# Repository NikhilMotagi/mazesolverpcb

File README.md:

#                                                                     MILLI MOUSE

This repo is for pcbs that were designed for mazesolver MILLIMOUSE (RIP)

The project went through many changes, some were minor some were major. Following are short discriptions about each design.

## MAZESOLVERWITHIR

u(mew)controller of choice was STM32F103C8T6 , because why not, it is faster than Arduino and has a bigger storage.

Here IR sensors acted as proximity sensors. They woud send signals when walls are in a given range.

RGB led was used to give indications and also to flash like police strobe light becuase why not *FLEXXXXXX*(later it was understood "why not").

MPU6050 was used to get orientations of the bot, so that perfect 90 degree turns could be performed.

Battery - 7.4V 2S lipo orange battery, a buck converter was used to step it down to 5V. 

Points to be noted--> 

1)IR won't always work as intended and calibaration is a nightmare as the readings change with ambient light.
2) Do not flip the PCB print while exporting PDF for both back copper. Only valid for text 

## MAZESOLVERSTM32_ULTRASONIC

KNOCK KNOCK 

Who's there ?

Ambient light 

IR's were not the greatest choice for checking distance, also there was concern about centering the bot.

SO here comes the new component HC-SR04!

The pcb had to be redesigned for ultrasonic and this time for good, the placement were done using dxf files from cad so everything was perfect.

Other unsophisticated yet time saving efforts were also explored(We all agreed pcb is the way to go).

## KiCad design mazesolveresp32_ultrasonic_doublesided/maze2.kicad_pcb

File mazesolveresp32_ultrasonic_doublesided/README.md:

This version of pcb has no component changes. A new thing that we tried was to design and fabricate a double sided pcb .
Points to be remebered are 
1) Keep the track width more than 1mm because these are not easy to DIY.
2) Remember to provide appropriate diameter vias when needed, professionally manufactured pcbs have revets that join both bottom and top layers.

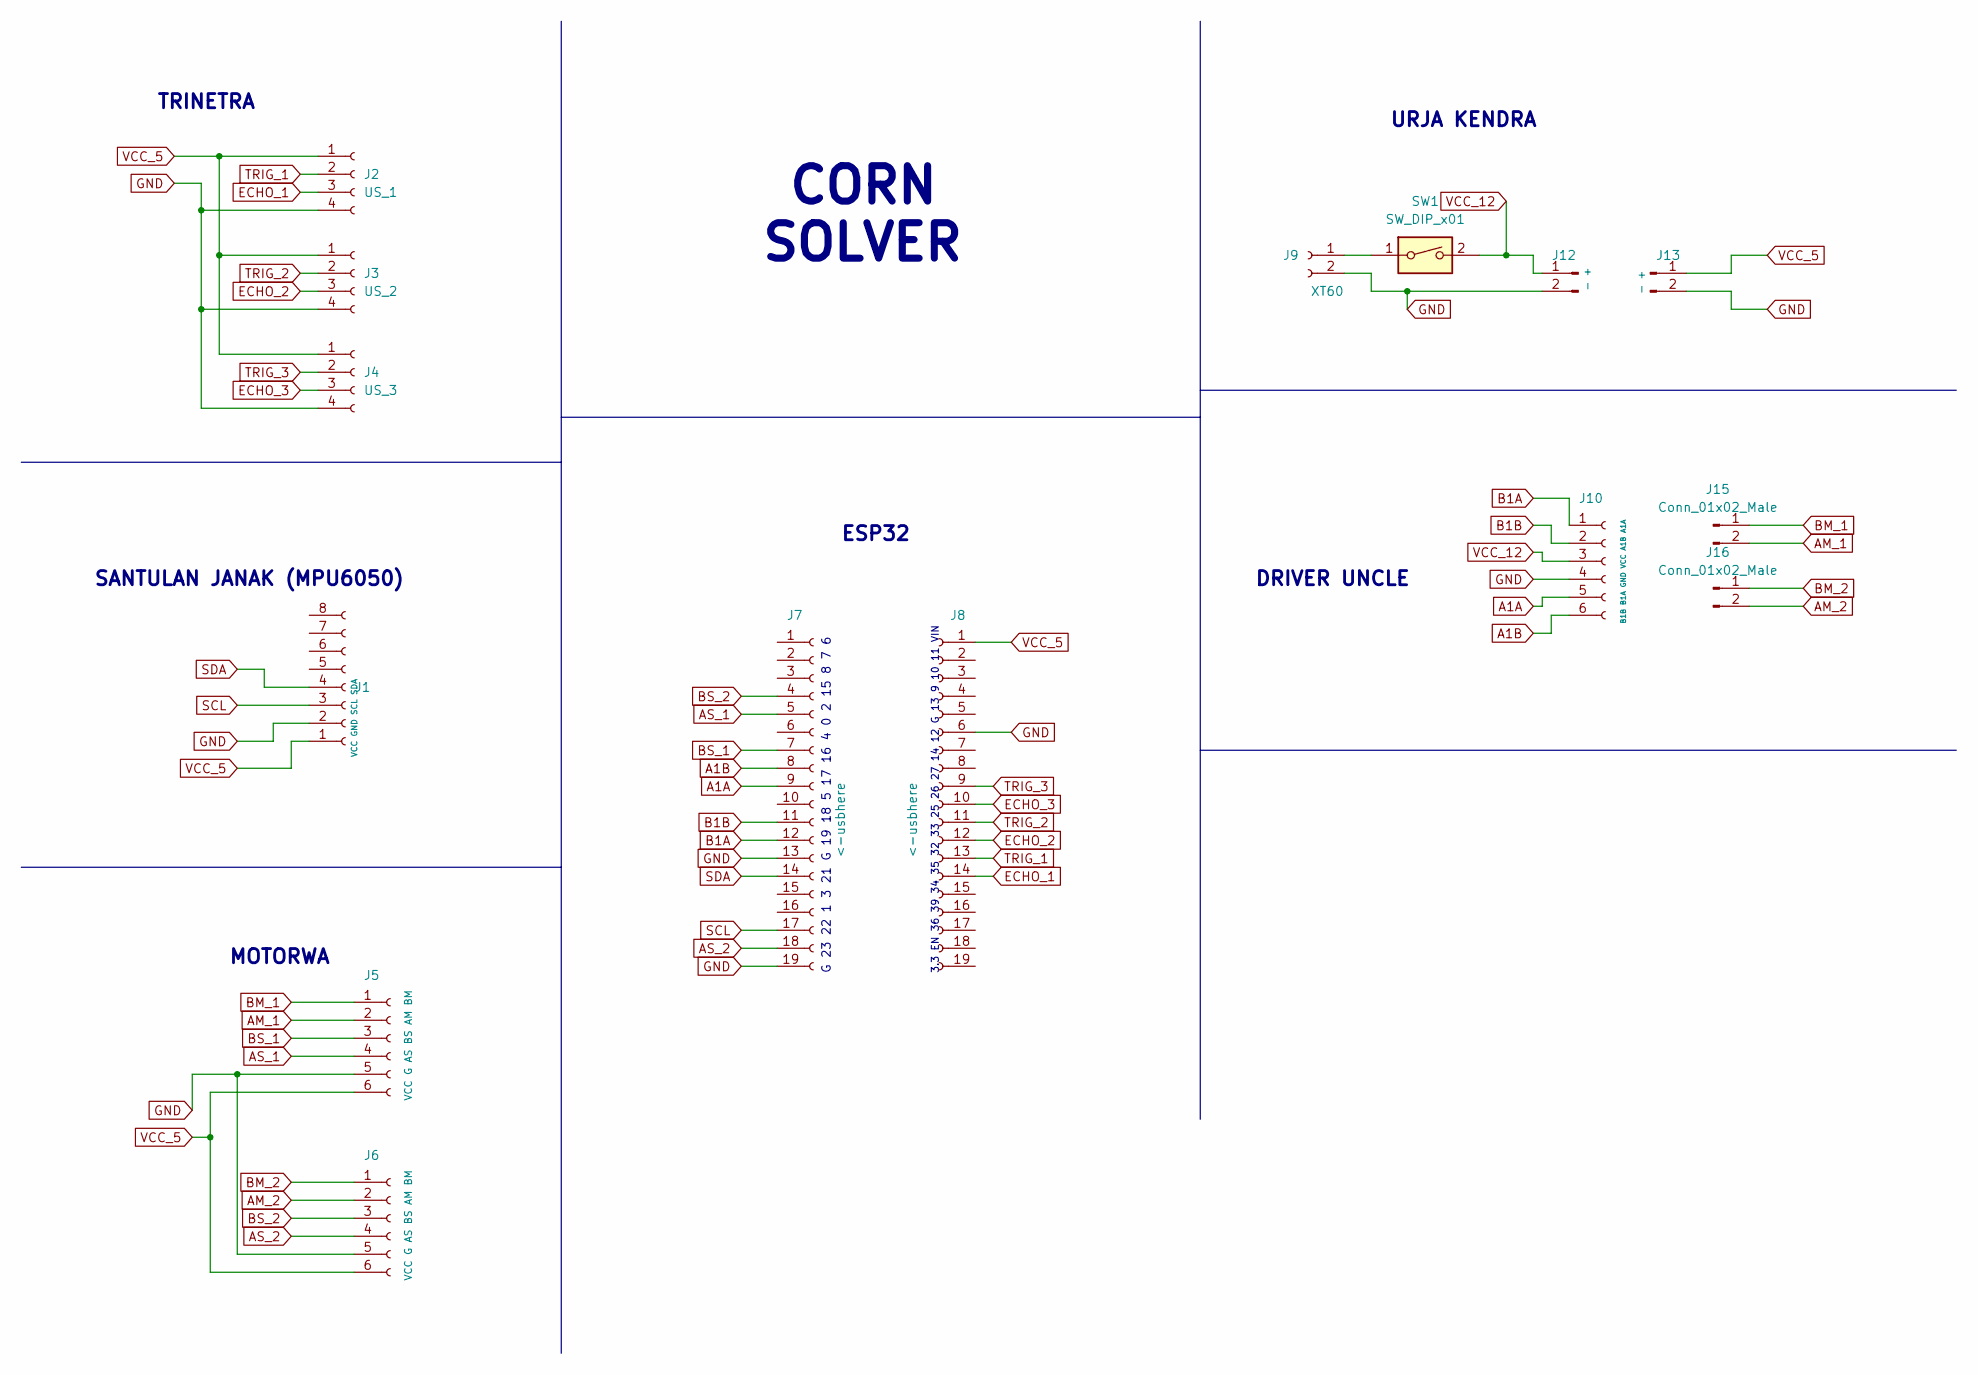
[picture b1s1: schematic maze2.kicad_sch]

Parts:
J1: VCC GND SCL SDA; PinSocket_1x08_P2.54mm_Vertical
J2: US_1; PinSocket_1x04_P2.54mm_Vertical
J3: US_2; PinSocket_1x04_P2.54mm_Vertical
J4: US_3; PinSocket_1x04_P2.54mm_Vertical
J5, J6: VCC G AS BS AM BM; PinHeader_1x06_P2.54mm_Vertical
J7, J8: <-usbhere; PinSocket_1x19_P2.54mm_Vertical
J9: XT60; AMASS_XT60-M_1x02_P7.20mm_Vertical
J10: B1B B1A GND VCC A1B A1A; PinSocket_1x06_P2.54mm_Vertical
J12, J13: - +; PinHeader_1x02_P2.54mm_Vertical
J15, J16: Conn_01x02_Male; PinSocket_1x02_P2.54mm_Vertical
SW1: SW_DIP_x01; DPDT_SW

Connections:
A1A: J7.9, J10.5
A1B: J7.8, J10.6
AM_1: J5.2, J15.2
AM_2: J6.2, J16.2
AS_1: J5.4, J7.5
AS_2: J6.4, J7.18
B1A: J7.12, J10.1
B1B: J7.11, J10.2
BM_1: J5.1, J15.1
BM_2: J6.1, J16.1
BS_1: J5.3, J7.7
BS_2: J6.3, J7.4
ECHO_1: J2.3, J8.14
ECHO_2: J3.3, J8.12
ECHO_3: J4.3, J8.10
GND: J1.2, J2.4, J3.4, J4.4, J5.5, J6.5, J7.13, J7.19, J8.6, J9.2, J10.4, J12.2, J13.2
unnamed: J9.1, SW1.1
SCL: J1.3, J7.17
SDA: J1.4, J7.14
TRIG_1: J2.2, J8.13
TRIG_2: J3.2, J8.11
TRIG_3: J4.2, J8.9
VCC_5: J1.1, J2.1, J3.1, J4.1, J5.6, J6.6, J8.1, J13.1
VCC_12: J10.3, J12.1, SW1.2

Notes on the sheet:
DRIVER UNCLE
3.3 EN 36 39 34 35 32 33 25 26 27 14 12 G 13 9 10 11 VIN
URJA KENDRA
CORN SOLVER
ESP32
G 23 22 1 3 21 G 19 18 5 17 16 4 0 2 15 8 7 6
SANTULAN JANAK (MPU6050)
MOTORWA
TRINETRA

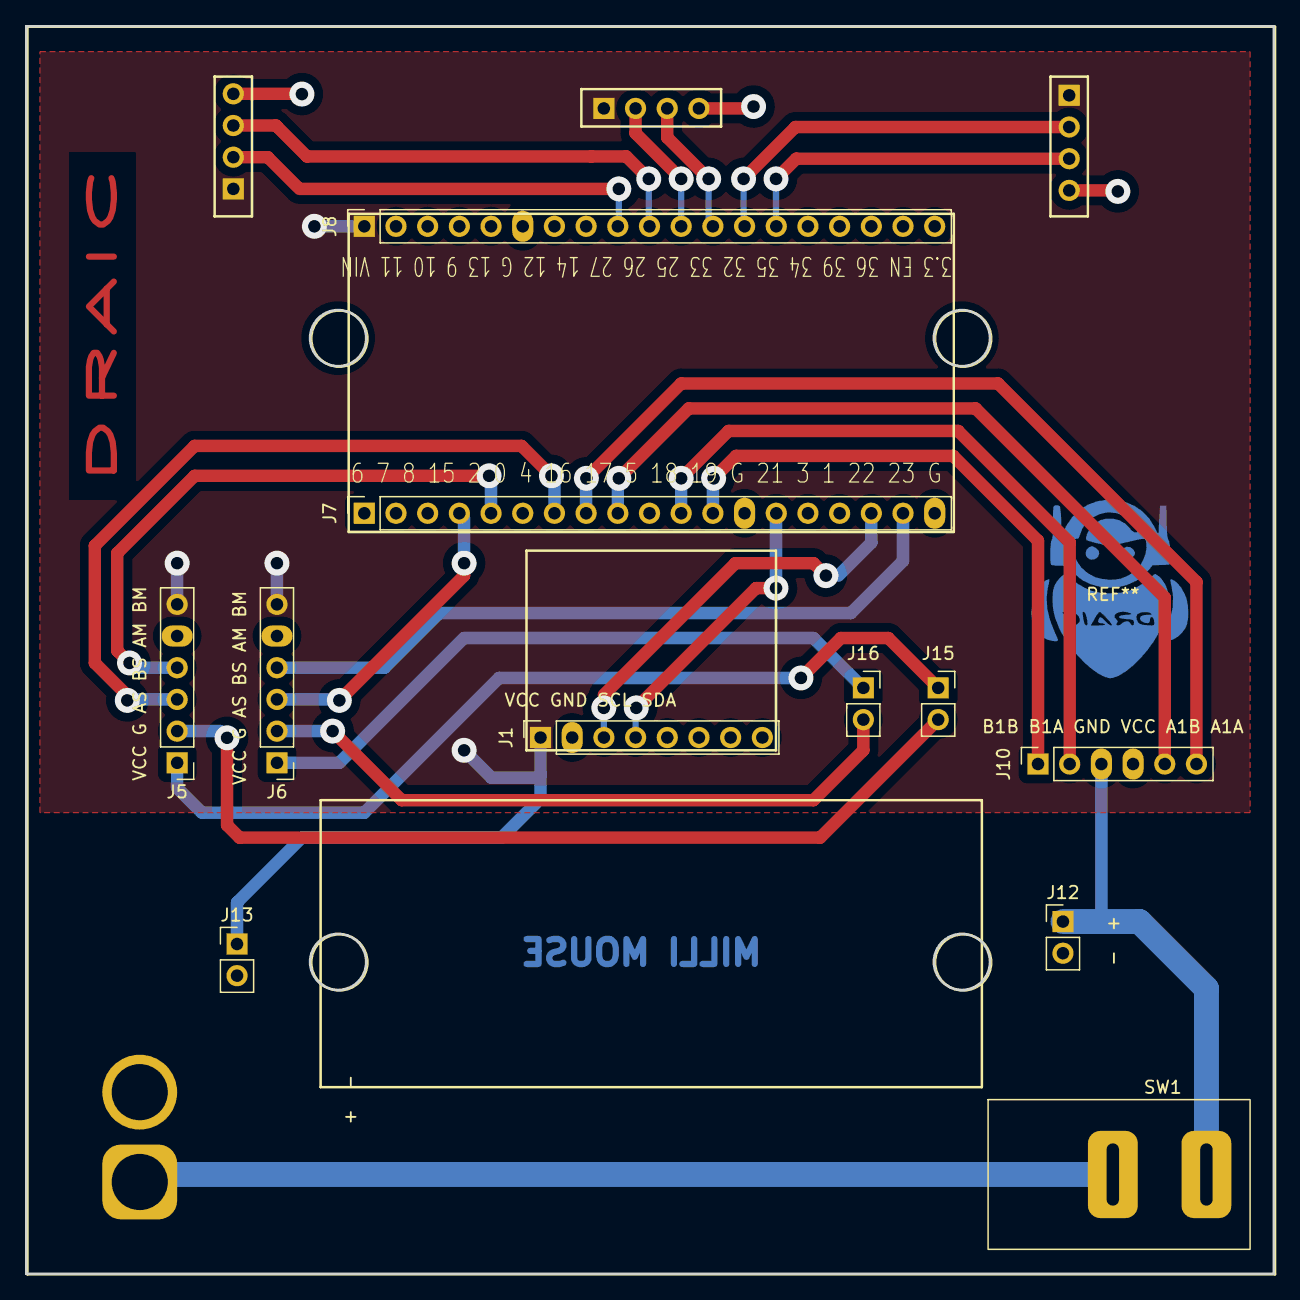
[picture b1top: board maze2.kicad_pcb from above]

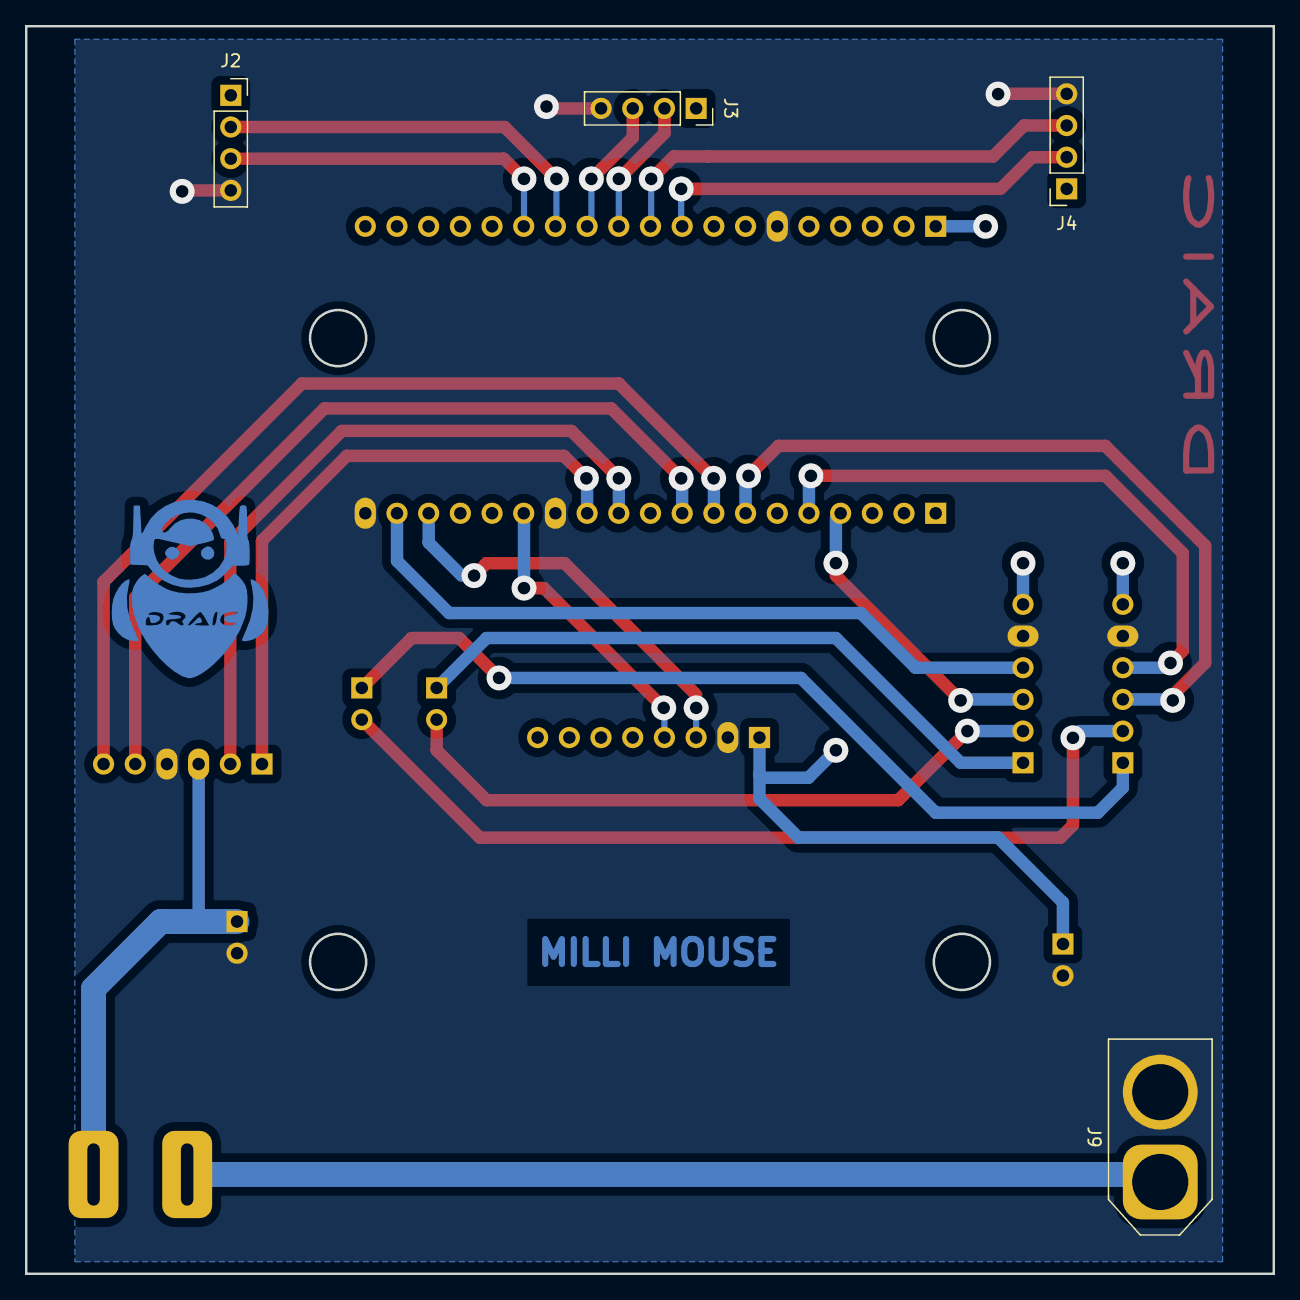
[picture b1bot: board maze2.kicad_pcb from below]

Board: 2 copper layers, 100.0 x 100.0 mm, 15 parts (4 on the bottom side), 24 nets.

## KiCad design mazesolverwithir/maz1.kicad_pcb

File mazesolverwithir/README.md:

The design inculdes stm32 microcontroller aka sasta controller, IR sensors, L9110s Motor driver, N20 encoder motors, MPU6050.

Working -
IR sensors are set to give signal for a certain distance. MPU is used to get angle of rotation for precise 90 degree turns. Encoder motors help in counting how far the 
bot has travelled 

STM32 is prefered because of it's high operation speed and comparatively good storage.

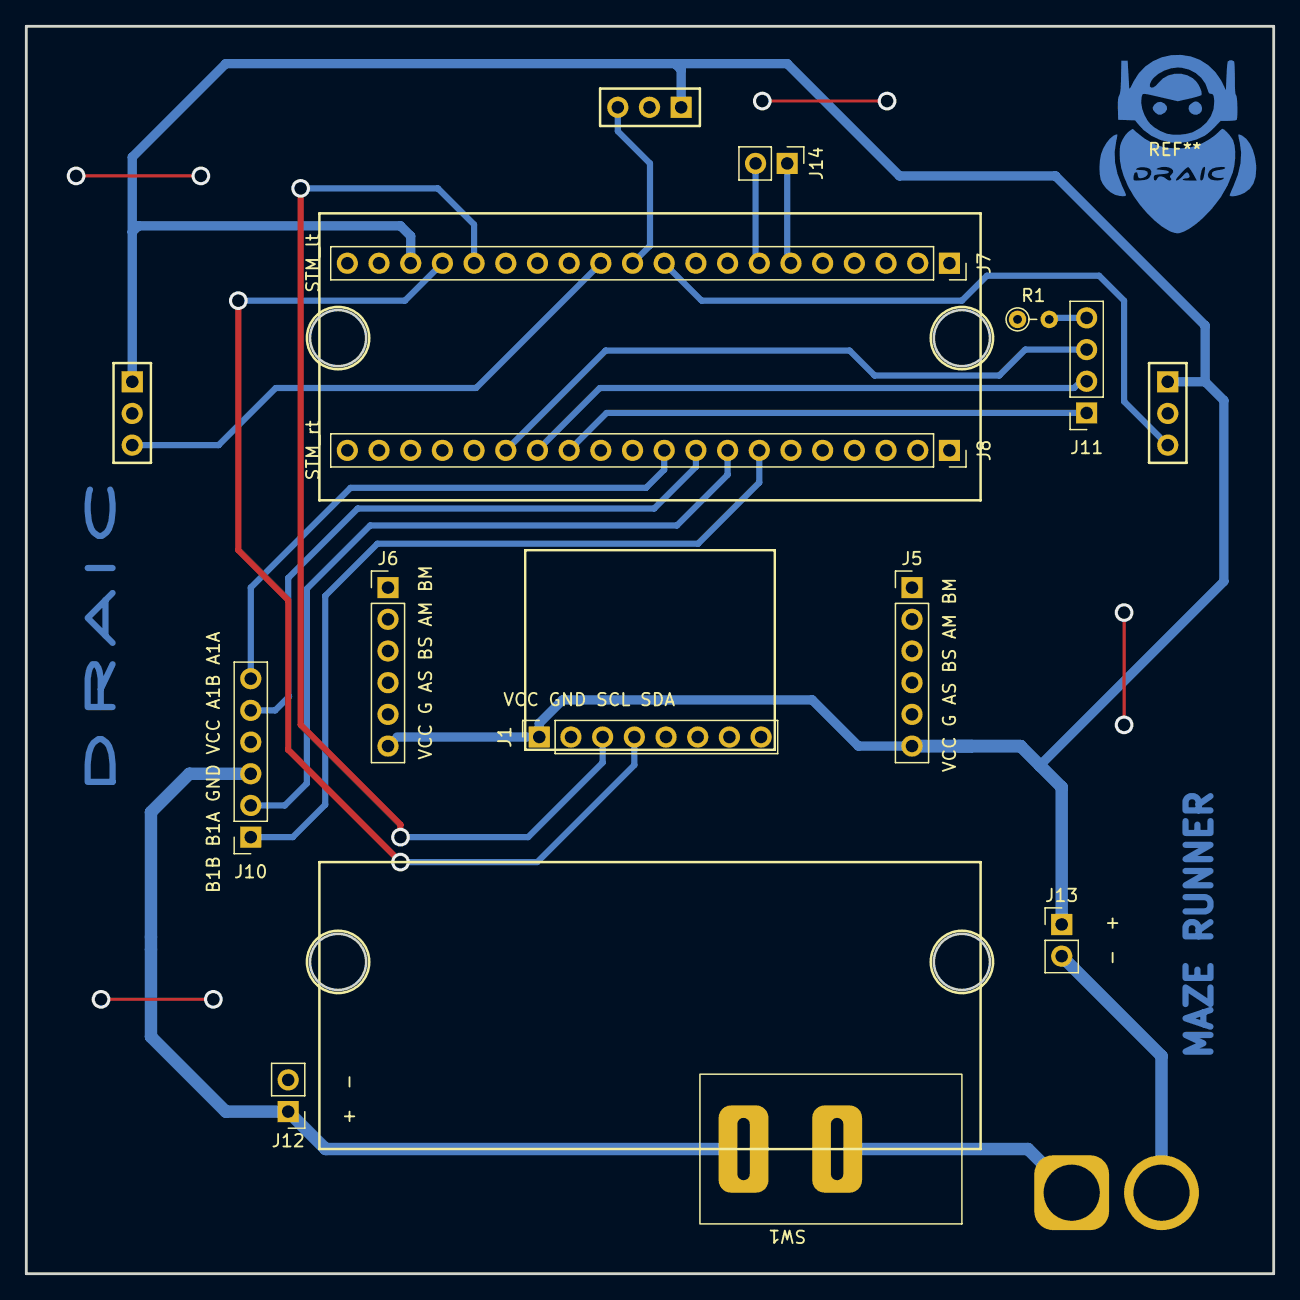
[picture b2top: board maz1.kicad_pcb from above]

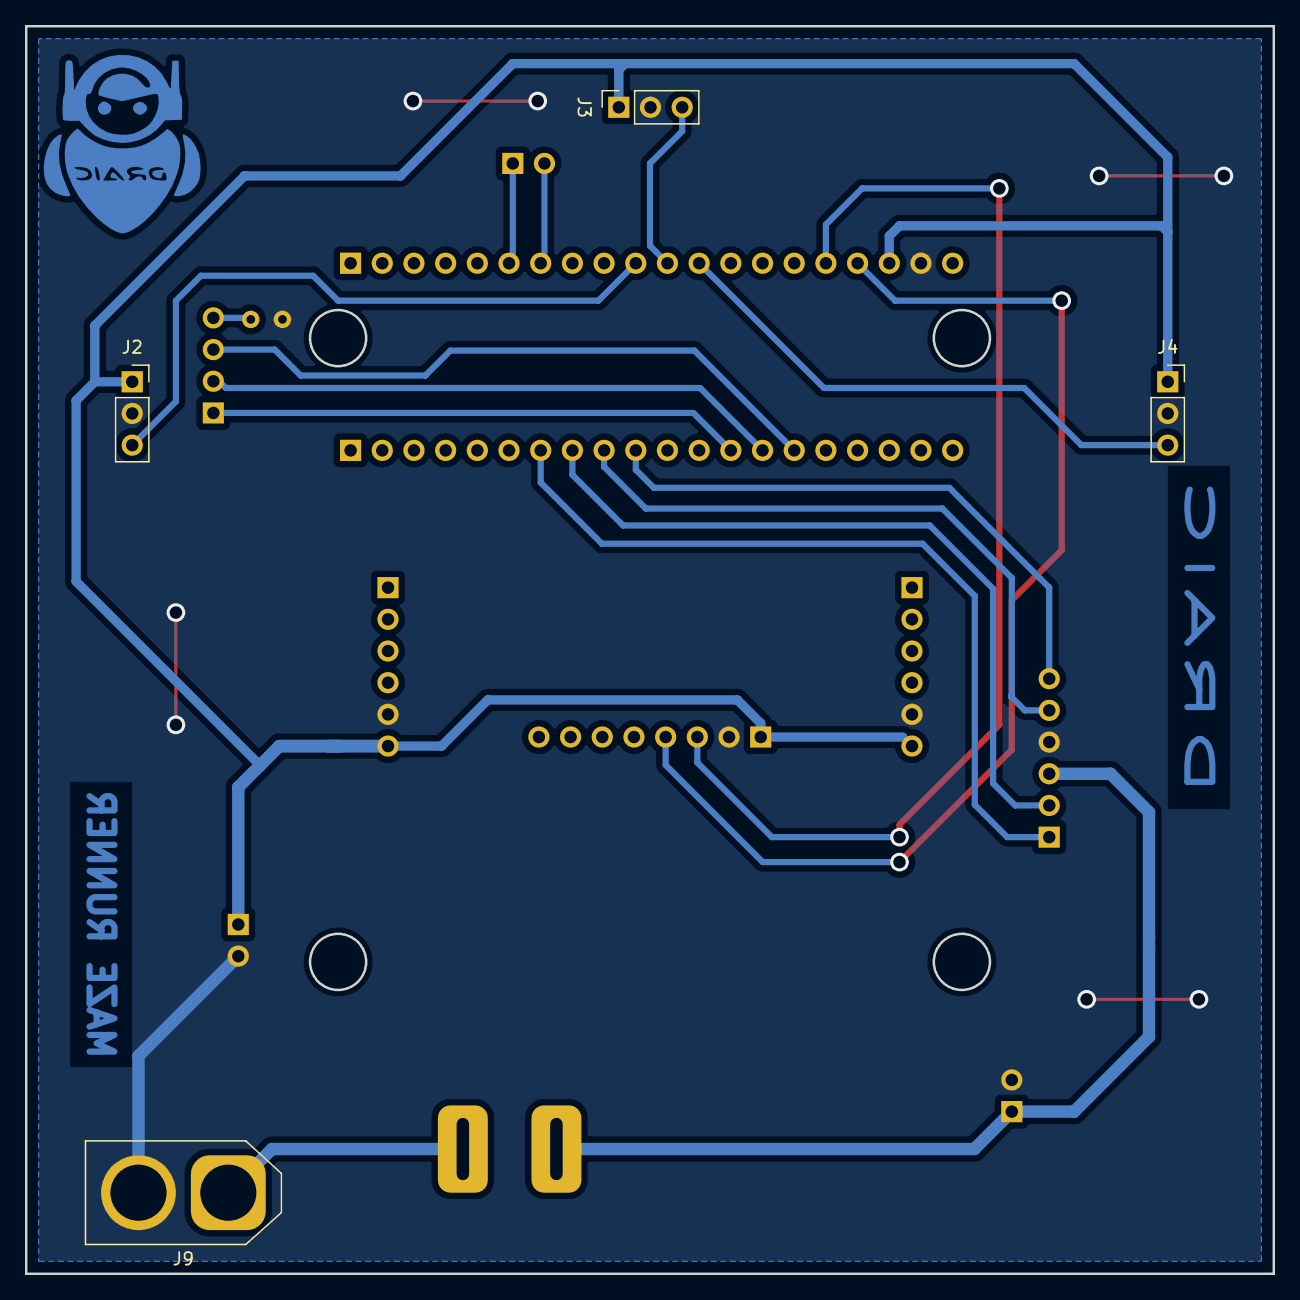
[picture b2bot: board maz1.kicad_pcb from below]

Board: 2 copper layers, 100.0 x 100.0 mm, 16 parts (4 on the bottom side), 19 nets.

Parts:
J1: VCC GND SCL SDA; PinSocket_1x08_P2.54mm_Vertical
J2: IR_1; PinSocket_1x03_P2.54mm_Vertical
J3: IR_2; PinSocket_1x03_P2.54mm_Vertical
J4: IR_3; PinSocket_1x03_P2.54mm_Vertical
J5, J6: VCC G AS BS AM BM; PinHeader_1x06_P2.54mm_Vertical
J7: STM_lt; PinSocket_1x20_P2.54mm_Vertical
J8: STM_rt; PinSocket_1x20_P2.54mm_Vertical
J9: XT60; AMASS_XT60-M_1x02_P7.20mm_Vertical
J10: B1B B1A GND VCC A1B A1A; PinSocket_1x06_P2.54mm_Vertical
J11: RGB; PinSocket_1x04_P2.54mm_Vertical
J12, J13: - +; PinHeader_1x02_P2.54mm_Vertical
J14: RX TX; PinHeader_1x02_P2.54mm_Vertical
R1: 220; R_Axial_DIN0204_L3.6mm_D1.6mm_P2.54mm_Vertical
SW1: SW_DIP_x01; DPDT_SW

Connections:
A1A: J8.9, J10.5
A1B: J8.10, J10.6
B: J8.15, J11.3
B1A: J8.7, J10.1
B1B: J8.8, J10.2
G: J8.14, J11.2
GND: J1.2, J2.2, J3.2, J4.2, J5.5, J6.5, J7.19, J9.2, J10.4, J12.2, J13.2, R1.1
IR_1: J2.3, J7.10
IR_2: J3.3, J7.11
IR_3: J4.3, J7.12
unnamed: J9.1, SW1.1
unnamed: J11.4, R1.2
unnamed: J7.6, J14.1
unnamed: J7.7, J14.2
R: J8.13, J11.1
SCL: J1.3, J7.16
SDA: J1.4, J7.17
VCC_5: J1.1, J2.1, J3.1, J4.1, J5.6, J6.6, J7.18, J13.1
VCC_12: J10.3, J12.1, SW1.2

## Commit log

2022-08-27 this is the first design
2022-08-27 next versions
2022-08-27 Rename mazesolveresp32_ultrasonic/maze.kicad_pcb to mazesolverstm32_ultrasonic/maze.kicad_pcb
2022-08-27 Rename mazesolveresp32_ultrasonic/maze.kicad_pro to mazesolverstm32_ultrasonic/maze.kicad_pro
2022-08-27 Rename mazesolveresp32_ultrasonic/maze.kicad_sch to mazesolverstm32_ultrasonic/maze.kicad_sch
2022-09-05 Update README.md
    edit 1
